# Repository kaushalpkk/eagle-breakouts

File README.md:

# eagle-breakout
A few eagle breakout board for SMD components

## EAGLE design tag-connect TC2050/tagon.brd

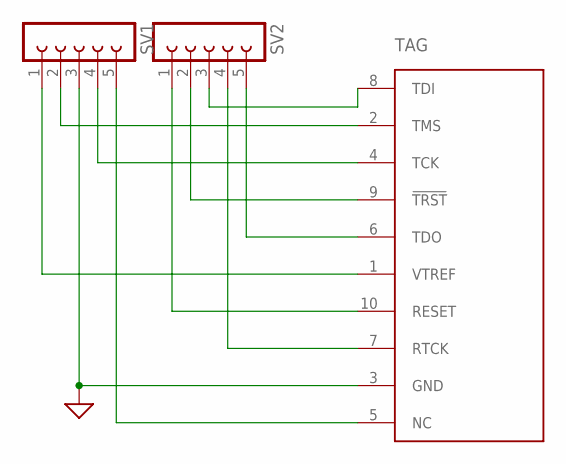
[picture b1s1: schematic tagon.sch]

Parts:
SV1, SV2: FE05-1
TAG: TC2050-MCP-NL; TC2030-MCP-NL

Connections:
GND: SV1.3, TAG.3 (GND)
unnamed: SV1.1, TAG.1 (VTREF)
unnamed: SV1.2, TAG.2 (TMS)
unnamed: SV1.4, TAG.4 (TCK)
unnamed: SV1.5, TAG.5 (NC)
unnamed: SV2.5, TAG.6 (TDO)
unnamed: SV2.4, TAG.7 (RTCK)
unnamed: SV2.3, TAG.8 (TDI)
unnamed: SV2.2, TAG.9 (!TRST)
unnamed: SV2.1, TAG.10 (RESET)

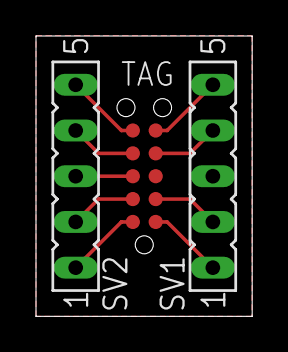
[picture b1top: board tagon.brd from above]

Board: 2 copper layers, 12.0 x 15.6 mm, 3 parts (0 on the bottom side), 10 nets.

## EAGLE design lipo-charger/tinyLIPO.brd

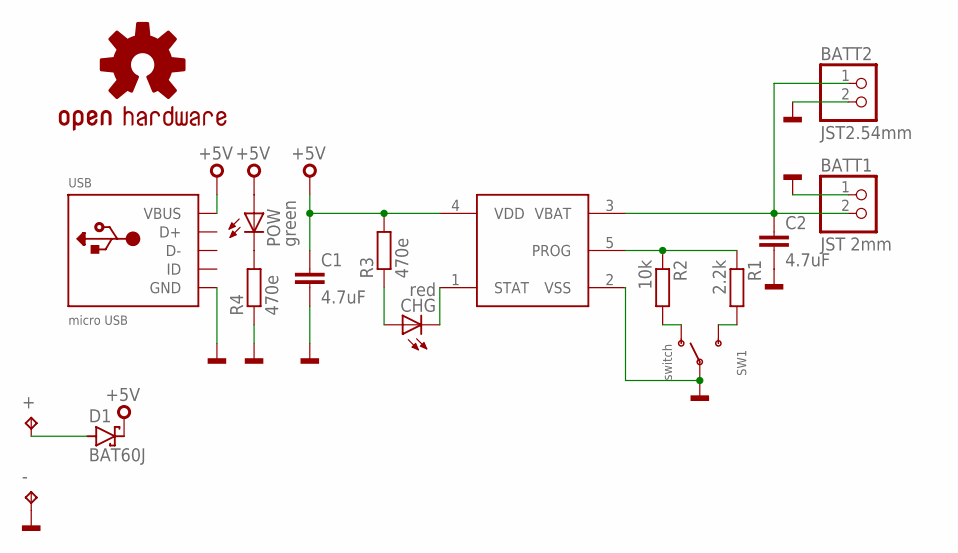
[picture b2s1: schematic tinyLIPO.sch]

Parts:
+: TPTP20SQ; TP20SQ
-: TPTP20SQ; TP20SQ
BATT1: JST 2mm; JSTPH2
BATT2: JST2.54mm; 1X02_OVAL
C1, C2: 4.7uF; C0805
CHG: red; CHIPLED_0805
D1: BAT60J; SOD323_ST
IC1: MCP73831; SOT23-5
LOGO1: OSHW-LOGOM; OSHW-LOGO-M
POW: green; CHIPLED_0805
R1: 2.2k; M0805
R2: 10k; M0805
R3, R4: 470e; M0805
SW1: switch; SPDT_SMT_SSSS811101
USB: micro USB; USB-MINIB_LARGER

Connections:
+5V: C1.1, D1.C, IC1.4 (VDD), POW.A, R3.2, USB.VBUS
GND: -.TP, BATT1.1, BATT2.2, C1.2, C2.2, IC1.2 (VSS), R4.1, SW1.B, USB.GND
unnamed: IC1.5 (PROG), R1.1, R2.1
unnamed: R1.2, SW1.C (S)
unnamed: R2.2, SW1.A (O)
unnamed: BATT1.2, BATT2.1, C2.1, IC1.3 (VBAT)
unnamed: CHG.A, R3.1
unnamed: CHG.C, IC1.1 (STAT)
unnamed: POW.C, R4.2
unnamed: +.TP, D1.A

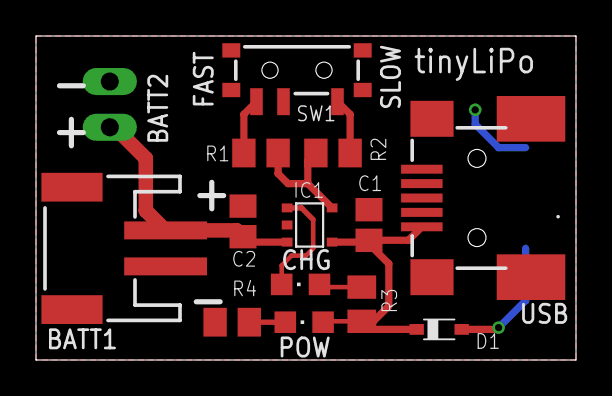
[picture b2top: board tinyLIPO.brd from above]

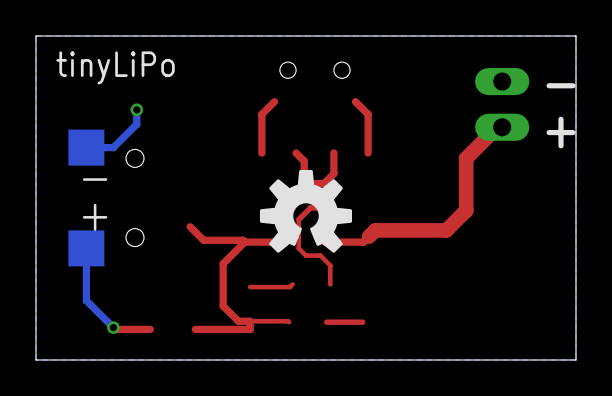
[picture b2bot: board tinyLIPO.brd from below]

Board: 2 copper layers, 30.0 x 18.0 mm, 17 parts (3 on the bottom side), 10 nets.

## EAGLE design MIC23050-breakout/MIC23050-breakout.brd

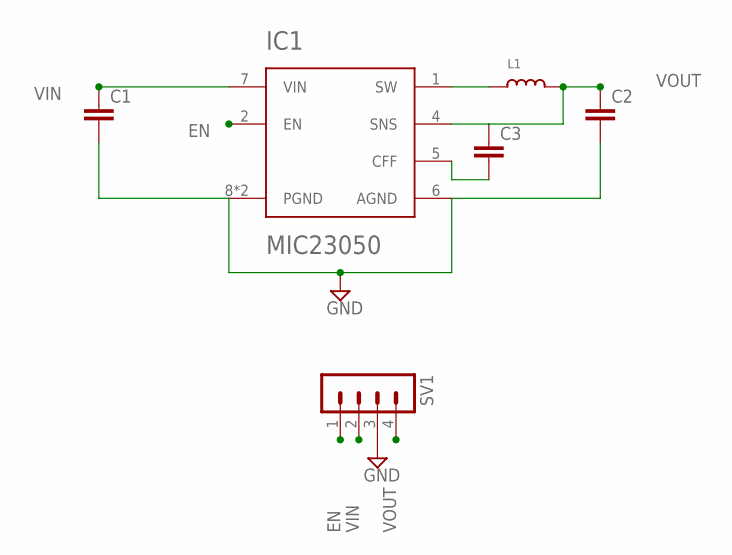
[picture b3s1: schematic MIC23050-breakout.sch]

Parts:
C1, C2, C3: C-EUC0603; C0603
IC1: MIC23050; MLF_2X2
L1: INDUCTOR0805; 0805
SV1: MA04-1

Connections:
EN: IC1.2 (EN), SV1.1
GND: C1.2, C2.2, IC1.6 (AGND), IC1.8 (PGND), IC1.9 (PGND), SV1.3
unnamed: C3.2, IC1.5 (CFF)
unnamed: IC1.1 (SW), L1.1
VIN: C1.1, IC1.7 (VIN), SV1.2
VOUT: C2.1, C3.1, IC1.4 (SNS), L1.2, SV1.4

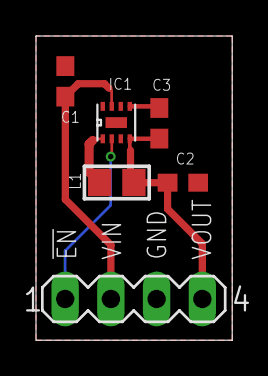
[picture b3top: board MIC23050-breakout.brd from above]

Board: 2 copper layers, 10.9 x 16.9 mm, 6 parts (0 on the bottom side), 6 nets.

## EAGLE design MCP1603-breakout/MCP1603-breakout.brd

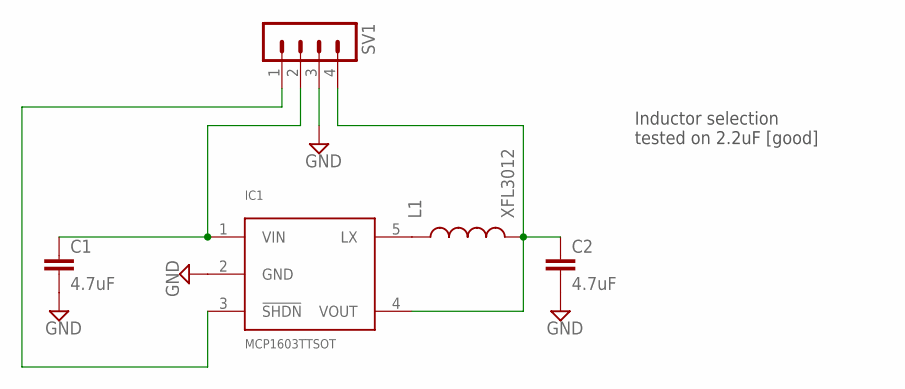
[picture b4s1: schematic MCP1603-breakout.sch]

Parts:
C1, C2: 4.7uF; C0603
IC1: MCP1603TTSOT; TSOT23-6
L1: XFL3012
SV1: MA04-1

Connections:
GND: C1.2, C2.2, IC1.2 (GND), SV1.3
unnamed: C1.1, IC1.1 (VIN), SV1.2
unnamed: C2.1, IC1.4 (VOUT), L1.2, SV1.4
unnamed: IC1.5 (LX), L1.1
unnamed: IC1.3 (!SHDN), SV1.1

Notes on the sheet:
Inductor selection tested on 2.2uF [good]

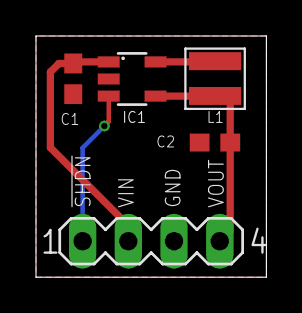
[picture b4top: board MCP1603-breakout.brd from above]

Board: 2 copper layers, 12.8 x 13.4 mm, 5 parts (0 on the bottom side), 5 nets.

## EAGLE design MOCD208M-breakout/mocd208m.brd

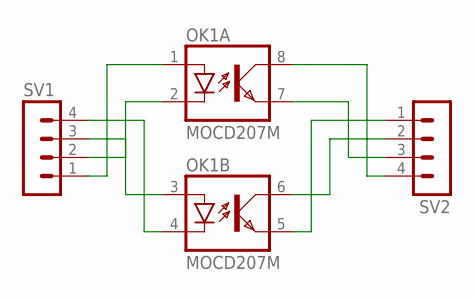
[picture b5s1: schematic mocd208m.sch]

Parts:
OK1: MOCD207M; SOIC08-FAIRCHILD
SV1, SV2: MA04-1

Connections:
unnamed: OK1.4 (C), SV1.4
unnamed: OK1.3 (A), SV1.3
unnamed: OK1.2 (C), SV1.2
unnamed: OK1.1 (A), SV1.1
unnamed: OK1.8 (COL), SV2.4
unnamed: OK1.7 (EMIT), SV2.3
unnamed: OK1.6 (COL), SV2.2
unnamed: OK1.5 (EMIT), SV2.1

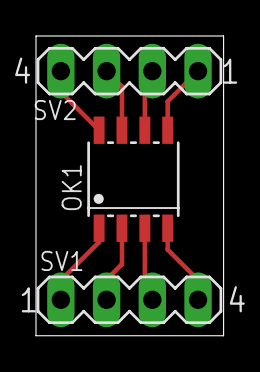
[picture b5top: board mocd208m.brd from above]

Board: 2 copper layers, 10.4 x 16.7 mm, 3 parts (0 on the bottom side), 8 nets.

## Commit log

2020-06-18 license change

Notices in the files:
parts and their libraries:
microbuilder: This work is placed in the public domain, and may be freely used for commercial and non-commercial work with the following conditions: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
SparkFun-Aesthetics: Licensing: Creative Commons ShareAlike 4.0 International - https://creativecommons.org/licenses/by-sa/4.0
TC2050: ©2009 ROFA.cz
